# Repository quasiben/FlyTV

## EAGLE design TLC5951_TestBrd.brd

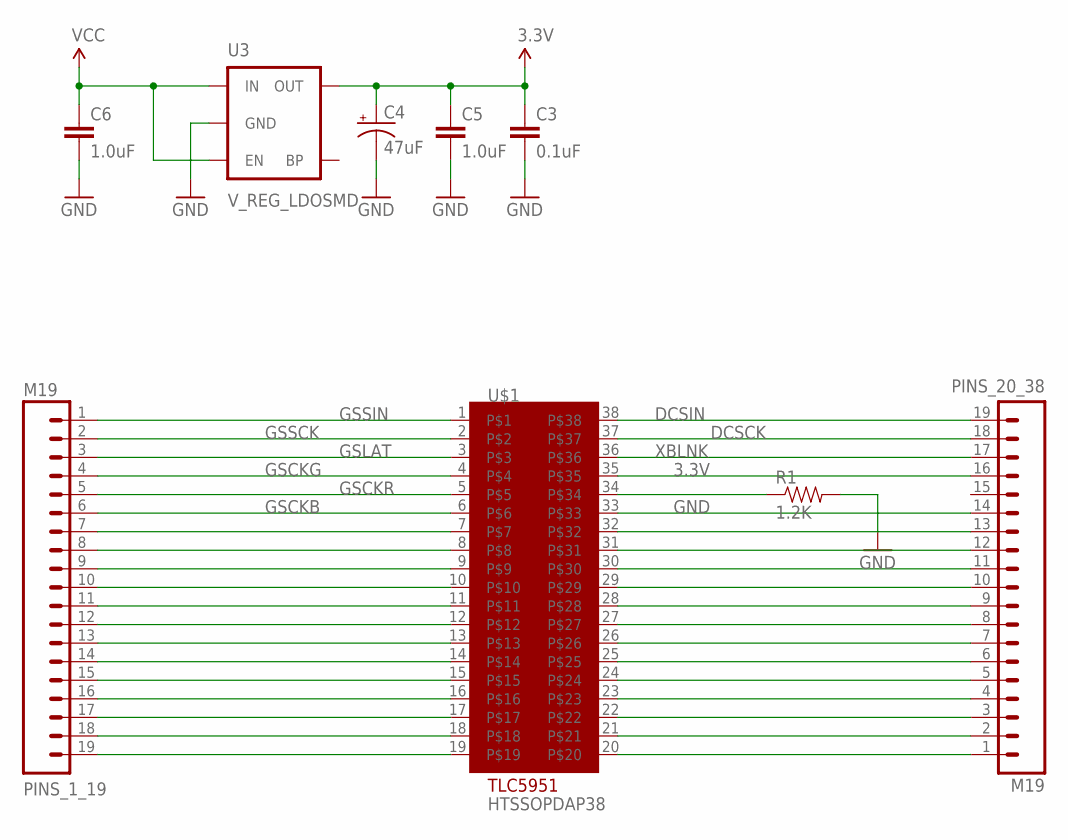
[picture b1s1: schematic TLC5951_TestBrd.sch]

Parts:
C3: 0.1uF; 0402-CAP
C4: 47uF; EIA3528
C5, C6: 1.0uF; 0402-CAP
PINS_1_19, PINS_20_38: M19; 1X19
R1: 1.2K; AXIAL-0.6
U3: V_REG_LDOSMD; SOT23-5
U$1: HTSSOPDAP38

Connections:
3.3V: C3.1, C4.A (+), C5.1, PINS_20_38.16, U3.5 (OUT), U$1.35
DCSCK: PINS_20_38.18, U$1.37
DCSIN: PINS_20_38.19, U$1.38
GND: C3.2, C4.C (-), C5.2, C6.2, PINS_20_38.14, R1.P$2 (2), U3.2 (GND), U$1.33
GSCKB: PINS_1_19.6, U$1.6
GSCKG: PINS_1_19.4, U$1.4
GSCKR: PINS_1_19.5, U$1.5
GSLAT: PINS_1_19.3, U$1.3
GSSCK: PINS_1_19.2, U$1.2
GSSIN: PINS_1_19.1, U$1.1
unnamed: PINS_20_38.13, U$1.32
unnamed: R1.P$1 (1), U$1.34
unnamed: PINS_20_38.12, U$1.31
unnamed: PINS_20_38.11, U$1.30
unnamed: PINS_20_38.10, U$1.29
unnamed: PINS_20_38.9, U$1.28
unnamed: PINS_20_38.8, U$1.27
unnamed: PINS_20_38.7, U$1.26
unnamed: PINS_20_38.6, U$1.25
unnamed: PINS_20_38.5, U$1.24
unnamed: PINS_20_38.4, U$1.23
unnamed: PINS_20_38.3, U$1.22
unnamed: PINS_20_38.2, U$1.21
unnamed: PINS_20_38.1, U$1.20
unnamed: PINS_1_19.7, U$1.7
unnamed: PINS_1_19.8, U$1.8
unnamed: PINS_1_19.9, U$1.9
unnamed: PINS_1_19.10, U$1.10
unnamed: PINS_1_19.11, U$1.11
unnamed: PINS_1_19.12, U$1.12
unnamed: PINS_1_19.13, U$1.13
unnamed: PINS_1_19.14, U$1.14
unnamed: PINS_1_19.15, U$1.15
unnamed: PINS_1_19.16, U$1.16
unnamed: PINS_1_19.17, U$1.17
unnamed: PINS_1_19.18, U$1.18
unnamed: PINS_1_19.19, U$1.19
VCC: C6.1, U3.1 (IN), U3.3 (EN)
XBLNK: PINS_20_38.17, U$1.36

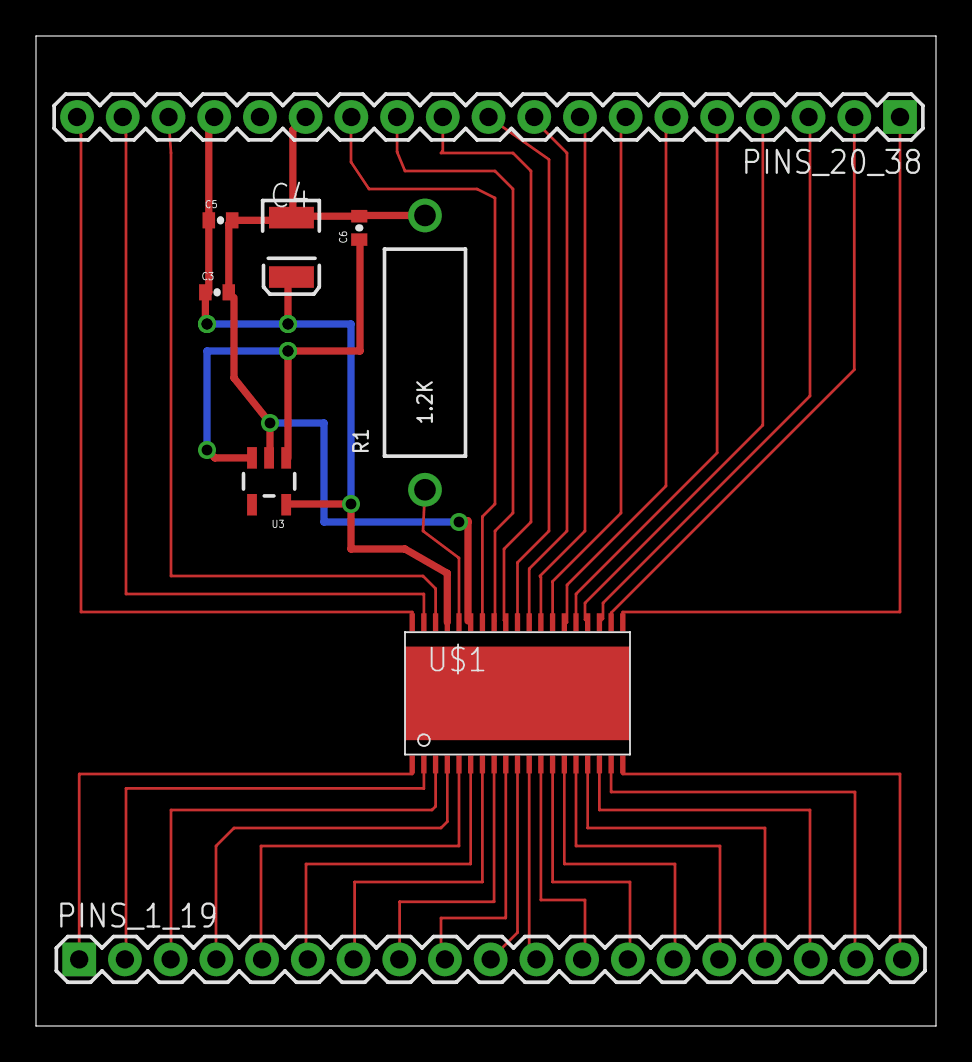
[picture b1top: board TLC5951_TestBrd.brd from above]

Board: 2 copper layers, 50.0 x 55.0 mm, 9 parts (0 on the bottom side), 39 nets.

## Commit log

2012-02-23 test commit of top level
2012-02-23 Notes on PCB for TI TLC5951
2012-02-23 Added initial comment
2012-03-15 Uploading a custom Eagle library and a schematic based on it.
    Created an Eagle Library for the TI TLC5951. Made an Eagle schematic
    with library component. Uploading both files.
2012-03-15 added data sheet tlc5951
2012-03-20 test new file
2012-03-20 added new LDO Voltage Regulator
2012-03-30 Updated TLC5951 Eagle library and Breakout Board Project File
    1. Updated TLC5951_DAP38 Eagle library by removing tsop under the
    central section of the chip, and by adding holes.
    2. Updated TLC5951_TestBrd schematic by adding headers and using new
    DAP38 device details
    3. Created TLC5951 layout with passive components and appropriate
    traces.
2012-03-30 Screen shot of breakout board
    Layout of TLC5951 breakout board
2012-03-30 Corrected a few minor ommissions
    1. Added three missing traces
    2. Made trace to Vcc pin on chip thinner to avoid bridging two pins
    3. The holes under the chip are now visible. Apparently I had not used
    the updated library file!?
2012-04-02 Added pin IDs on tPlace layer (top silkscreen)
2012-05-16 added matlab code for timing output
2012-05-16 Moved some files around and updated one Matlab and Arduino file.
    Moved some files into their appropriate directories.
    Added the current version of the Matlab code.
    Added the current version of the Arduino code.
2012-05-17 Updated Matlab code
    Finished the construction of the digital signals. The data lines, GSSIN
    and DCSIN, are twice the length of the clocked lines.

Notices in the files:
parts and their libraries:
SparkFun-Passives: Licensing: CC v3.0 Share-Alike You are welcome to use this library for commercial purposes.
